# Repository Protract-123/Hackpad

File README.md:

# Media Macropad

This is my submission for Hackpad! Has the following very cool features

- 2 Neopixels
- A 128x32 OLED screen
- 9 keys in a 3x3 orientation
- KMK firmware

## Schematic

Here's a picture of the schematic

## PCB

I had to rework the PCB traces a few times to make space for mounting holes, but it worked out in the end. The dimensions of the PCB are 99x95 (WxH)

## CAD

Was relatively painless to make the case once I finalised my PCB design, the only issue was I went back and forth a few times.

Here's the base and the shell of the case as individual parts.

## Firmware

The firmware was build with KMK and Python. The screen is unimplemented as of now, but will be Soon™.
There is now a better, alternative firmware created with QMK which also supports [KIN](https://github.com/Protract-123/KIN) to send information to the keyboard (Use the non-via one)

## Bill of Materials

Parts:

- 9x Cherry MX Switches
- 2x SK6812 MINI Leds
- 1x XIAO RP2040
- 9x Blank DSA Keycaps
- 4x M3x16 screws
- 4x M3x8 screws
- 8x M3 Heatset
- 9x Through-hole 1N4148 Diodes
- 1x EC11 Rotary encoder
- 1x 128x32 0.91 inch OLED display

Other Stuff:

- The PCB
- The Case, comprised of two 3D printed parts

## Credits

Here's a list of libraries and resources I used to create my hackpad

### Kicad Libraries

- XIAO footprints/schematics - <https://github.com/Seeed-Studio/OPL_Kicad_Library>
- 0.91 OLED Display footprints - <https://github.com/gorbachev/KiCad-SSD1306-0.91-OLED-4pin-128x32.pretty>
- Rotary Encoder footprints - <https://kicad.github.io/footprints/Rotary_Encoder>

### 3D Models

- SK6812 LED - <https://grabcad.com/library/sk6812-mini-sk6814-smd3535-1>
- Cherry MX Switches - <https://grabcad.com/library/cherry-mx-switches-mx-1>
- Rotary Encoder - <https://grabcad.com/library/rotary-encoder-17>
- OLED Display - <https://grabcad.com/library/display-oled128x32-1>
- XIAO RP2040 - <https://grabcad.com/library/seeed-studio-xiao-rp2040-1>

### Tutorials/References

- Duccs Fidget Toy - <https://github.com/hackclub/hackpad/tree/main/hackpads/Duccs%20Fidget%20Toy>
- Cyao's Mega Macropad - <https://github.com/hackclub/hackpad/tree/main/hackpads/cyaopad>
- Orpheuspad - <https://github.com/hackclub/hackpad/blob/main/hackpads/orpheuspad/pcb/.gitignore>
- Joe Scotto's PCB Design Video - <https://www.youtube.com/watch?v=8WXpGTIbxlQ>
- KMK Docs - <https://github.com/KMKfw/kmk_firmware/tree/main/docs/en>

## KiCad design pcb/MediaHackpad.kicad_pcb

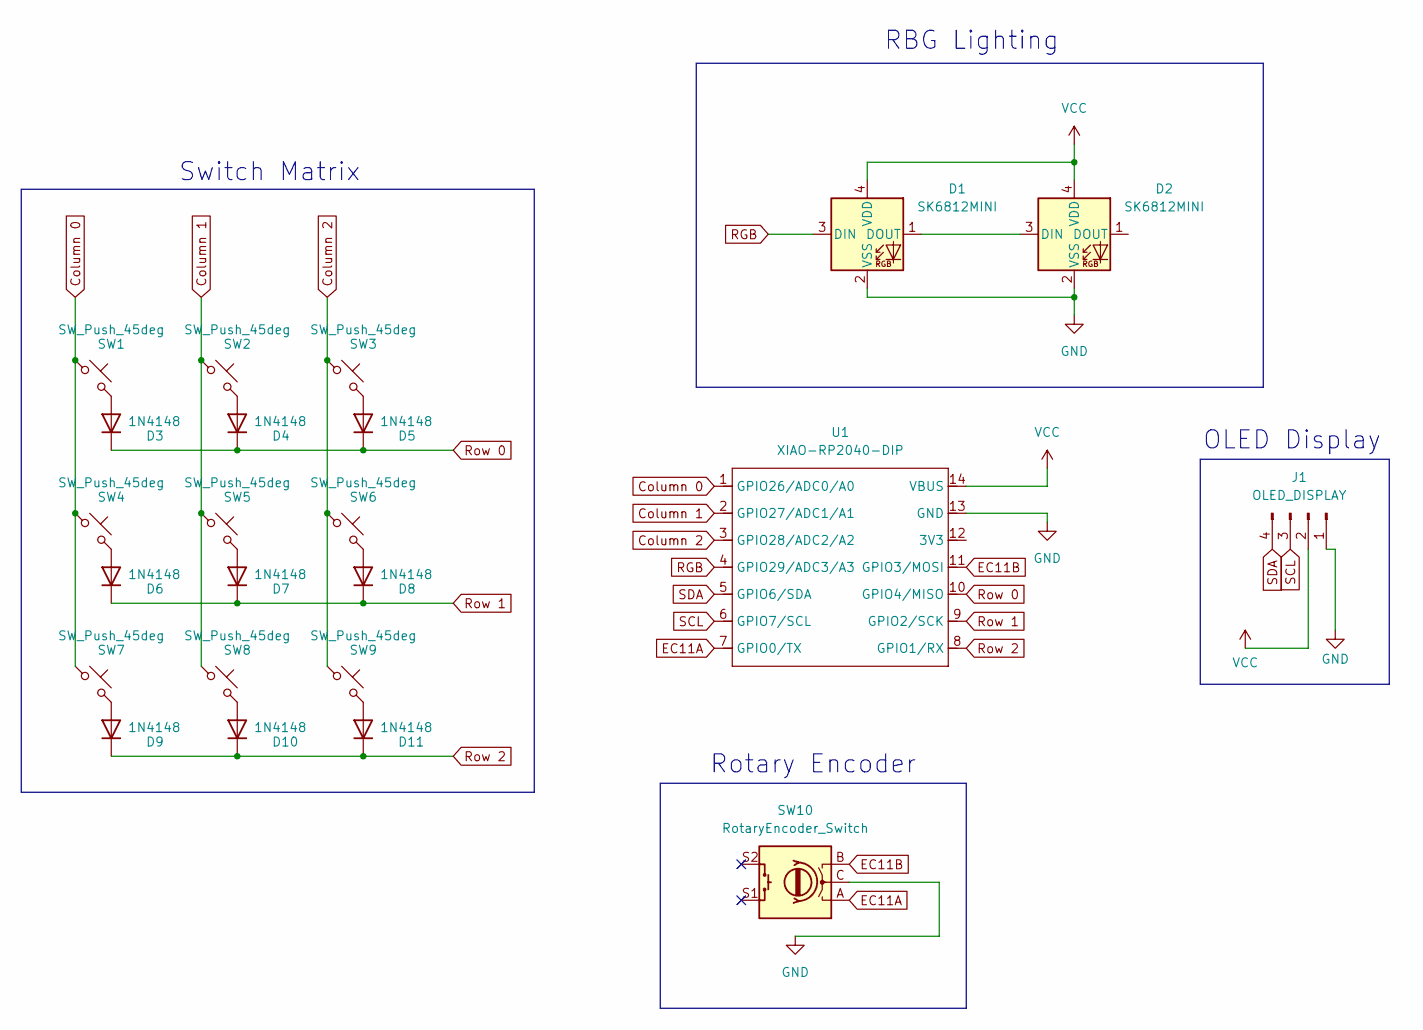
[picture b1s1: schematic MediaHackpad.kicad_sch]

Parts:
D1, D2: SK6812MINI; LED_SK6812MINI_PLCC4_3.5x3.5mm_P1.75mm
D3, D4, D5, D6, D7, D8, D9, D10, D11: 1N4148; D_DO-35_SOD27_P7.62mm_Horizontal
J1: OLED_DISPLAY; SSD1306-0.91-OLED-4pin-128x32
SW1, SW2, SW3, SW4, SW5, SW6, SW7, SW8, SW9: SW_Push_45deg; SW_Cherry_MX_1.00u_PCB
SW10: RotaryEncoder_Switch; RotaryEncoder_Alps_EC11E-Switch_Vertical_H20mm
U1: XIAO-RP2040-DIP

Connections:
Column 0: SW1.1, SW4.1, SW7.1, U1.1 (GPIO26/ADC0/A0)
Column 1: SW2.1, SW5.1, SW8.1, U1.2 (GPIO27/ADC1/A1)
Column 2: SW3.1, SW6.1, SW9.1, U1.3 (GPIO28/ADC2/A2)
EC11A: SW10.A, U1.7 (GPIO0/TX)
EC11B: SW10.B, U1.11 (GPIO3/MOSI)
GND: D1.2 (VSS), D2.2 (VSS), J1.1, SW10.C, U1.13 (GND)
unnamed: D1.1 (DOUT), D2.3 (DIN)
unnamed: D3.2 (A), SW1.2
unnamed: D4.2 (A), SW2.2
unnamed: D5.2 (A), SW3.2
unnamed: D6.2 (A), SW4.2
unnamed: D7.2 (A), SW5.2
unnamed: D8.2 (A), SW6.2
unnamed: D9.2 (A), SW7.2
unnamed: D10.2 (A), SW8.2
unnamed: D11.2 (A), SW9.2
RGB: D1.3 (DIN), U1.4 (GPIO29/ADC3/A3)
Row 0: D3.1 (K), D4.1 (K), D5.1 (K), U1.10 (GPIO4/MISO)
Row 1: D6.1 (K), D7.1 (K), D8.1 (K), U1.9 (GPIO2/SCK)
Row 2: D9.1 (K), D10.1 (K), D11.1 (K), U1.8 (GPIO1/RX)
SCL: J1.3, U1.6 (GPIO7/SCL)
SDA: J1.4, U1.5 (GPIO6/SDA)
VCC: D1.4 (VDD), D2.4 (VDD), J1.2, U1.14 (VBUS)

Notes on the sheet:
Rotary Encoder
OLED Display
Switch Matrix
RBG Lighting

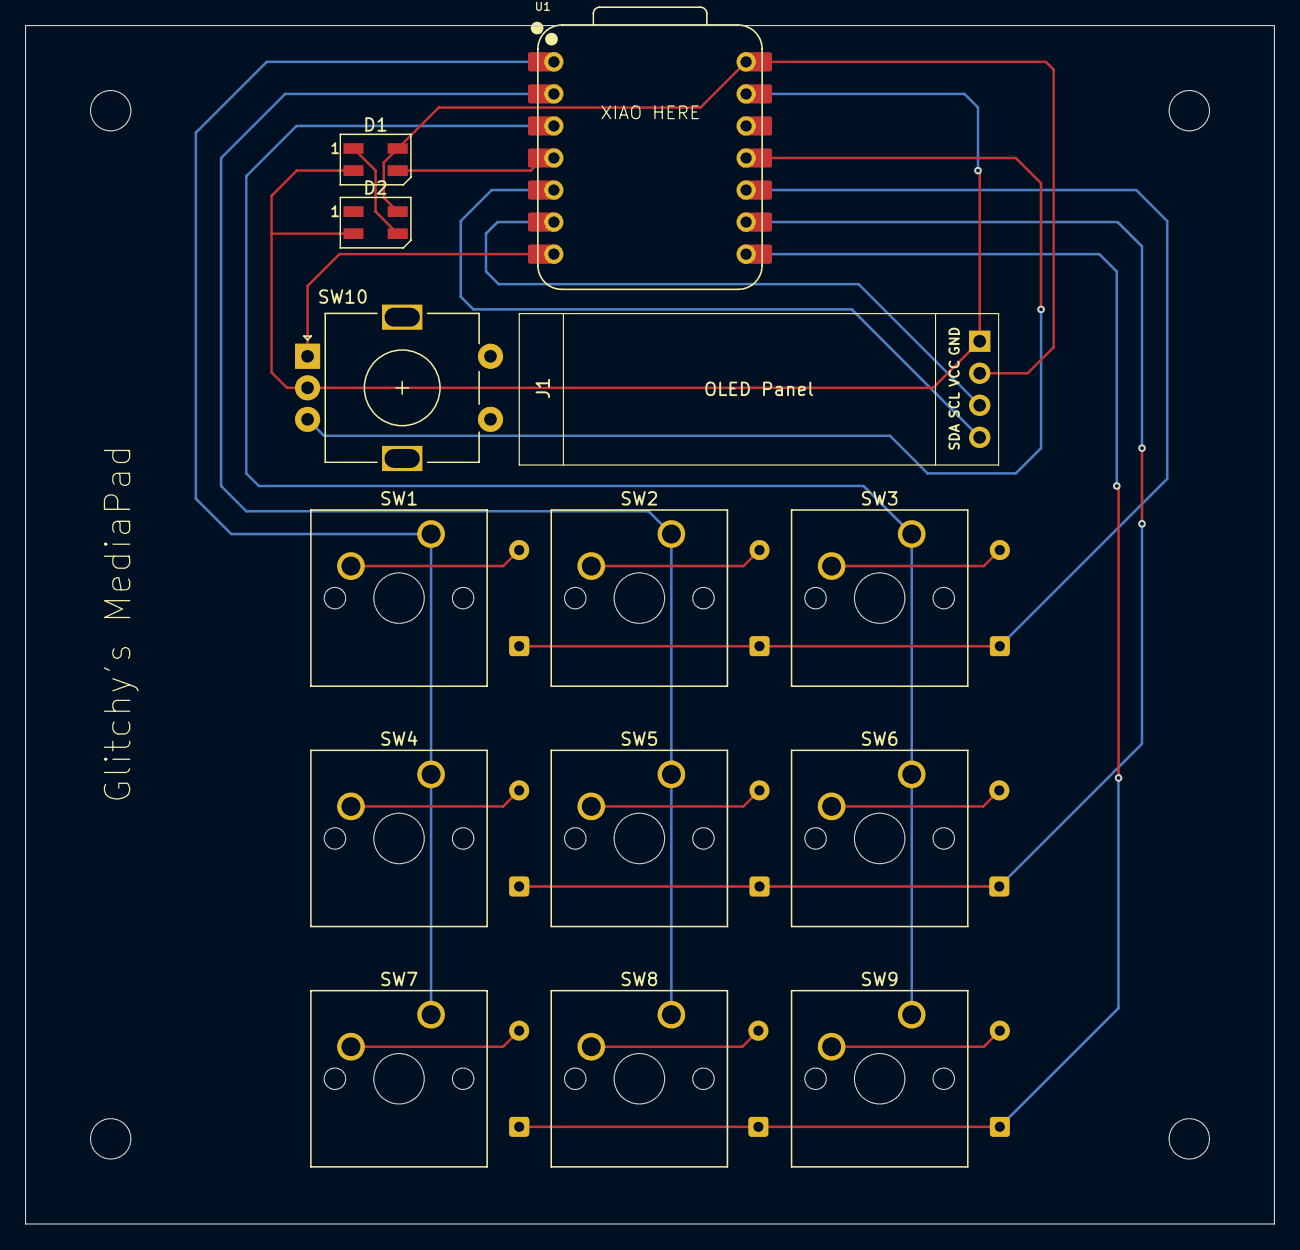
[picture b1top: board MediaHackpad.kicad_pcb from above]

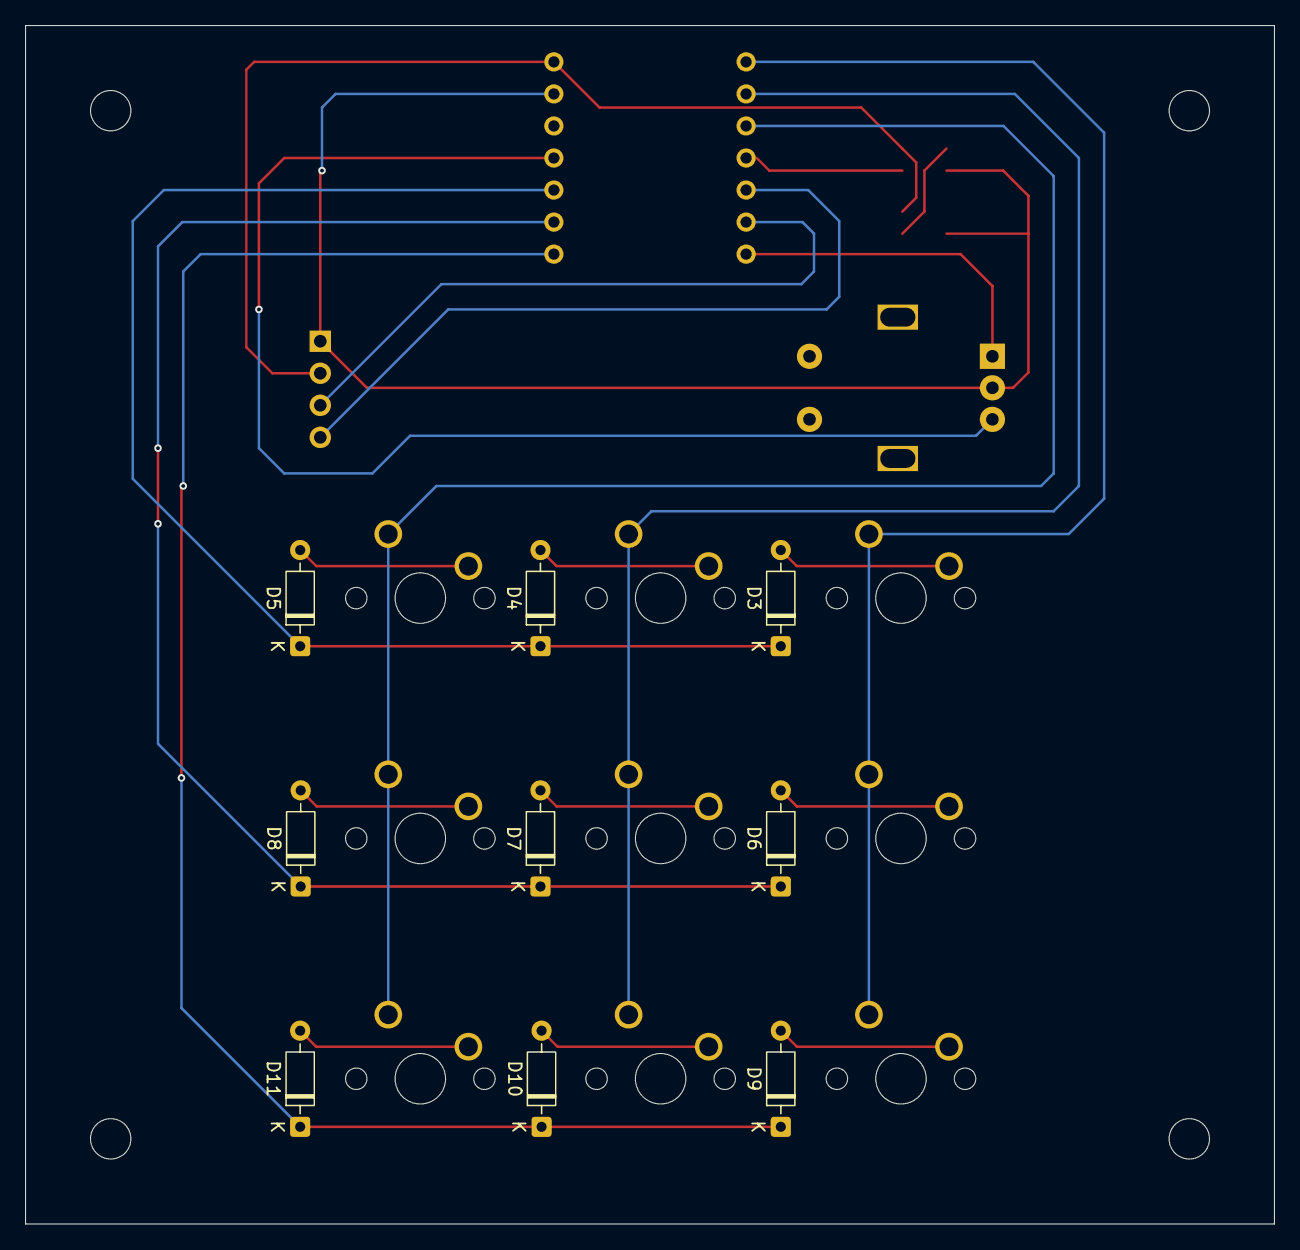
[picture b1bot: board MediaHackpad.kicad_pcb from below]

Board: 2 copper layers, 99.0 x 95.0 mm, 23 parts (9 on the bottom side), 23 nets.

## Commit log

2025-11-30 Upload Hackpad
2025-12-30 Firmware Update
2026-01-06 Display Text
2026-01-06 Upload Alternate Case
2026-01-25 Add QMK firmware with KIN support
2026-01-25 Add Github links to README
2026-02-19 Update Firmware for KIN changes
